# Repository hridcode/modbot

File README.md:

# ModBot

ModBot is a versatile RP2040 development board/robot base for mini robots. It is relatively small (~80x50mm), but packs a punch.

# Features

- RP2040 chip
- 2 L293D IC motor drivers (capable of driving 4 motors)
- MPU-6050 gyroscope + accelerometer IC
- 12 digital GPIO expansion pins 
- 4 ADC GPIO expansion pins
- 16 connections each for GND, +3.3V, and +5V (VBUS)
- Battery connection
- USB-C support (bare minimum for 2026)

# Pictures

|Schematic|PCB|
|---|---|
|||

# Notes

- If you are to use a battery with the board, you must include your own charging board and switch.
- I don't do FRC/FTC so I don't know if this would be something you can use for that.

---

Have fun!

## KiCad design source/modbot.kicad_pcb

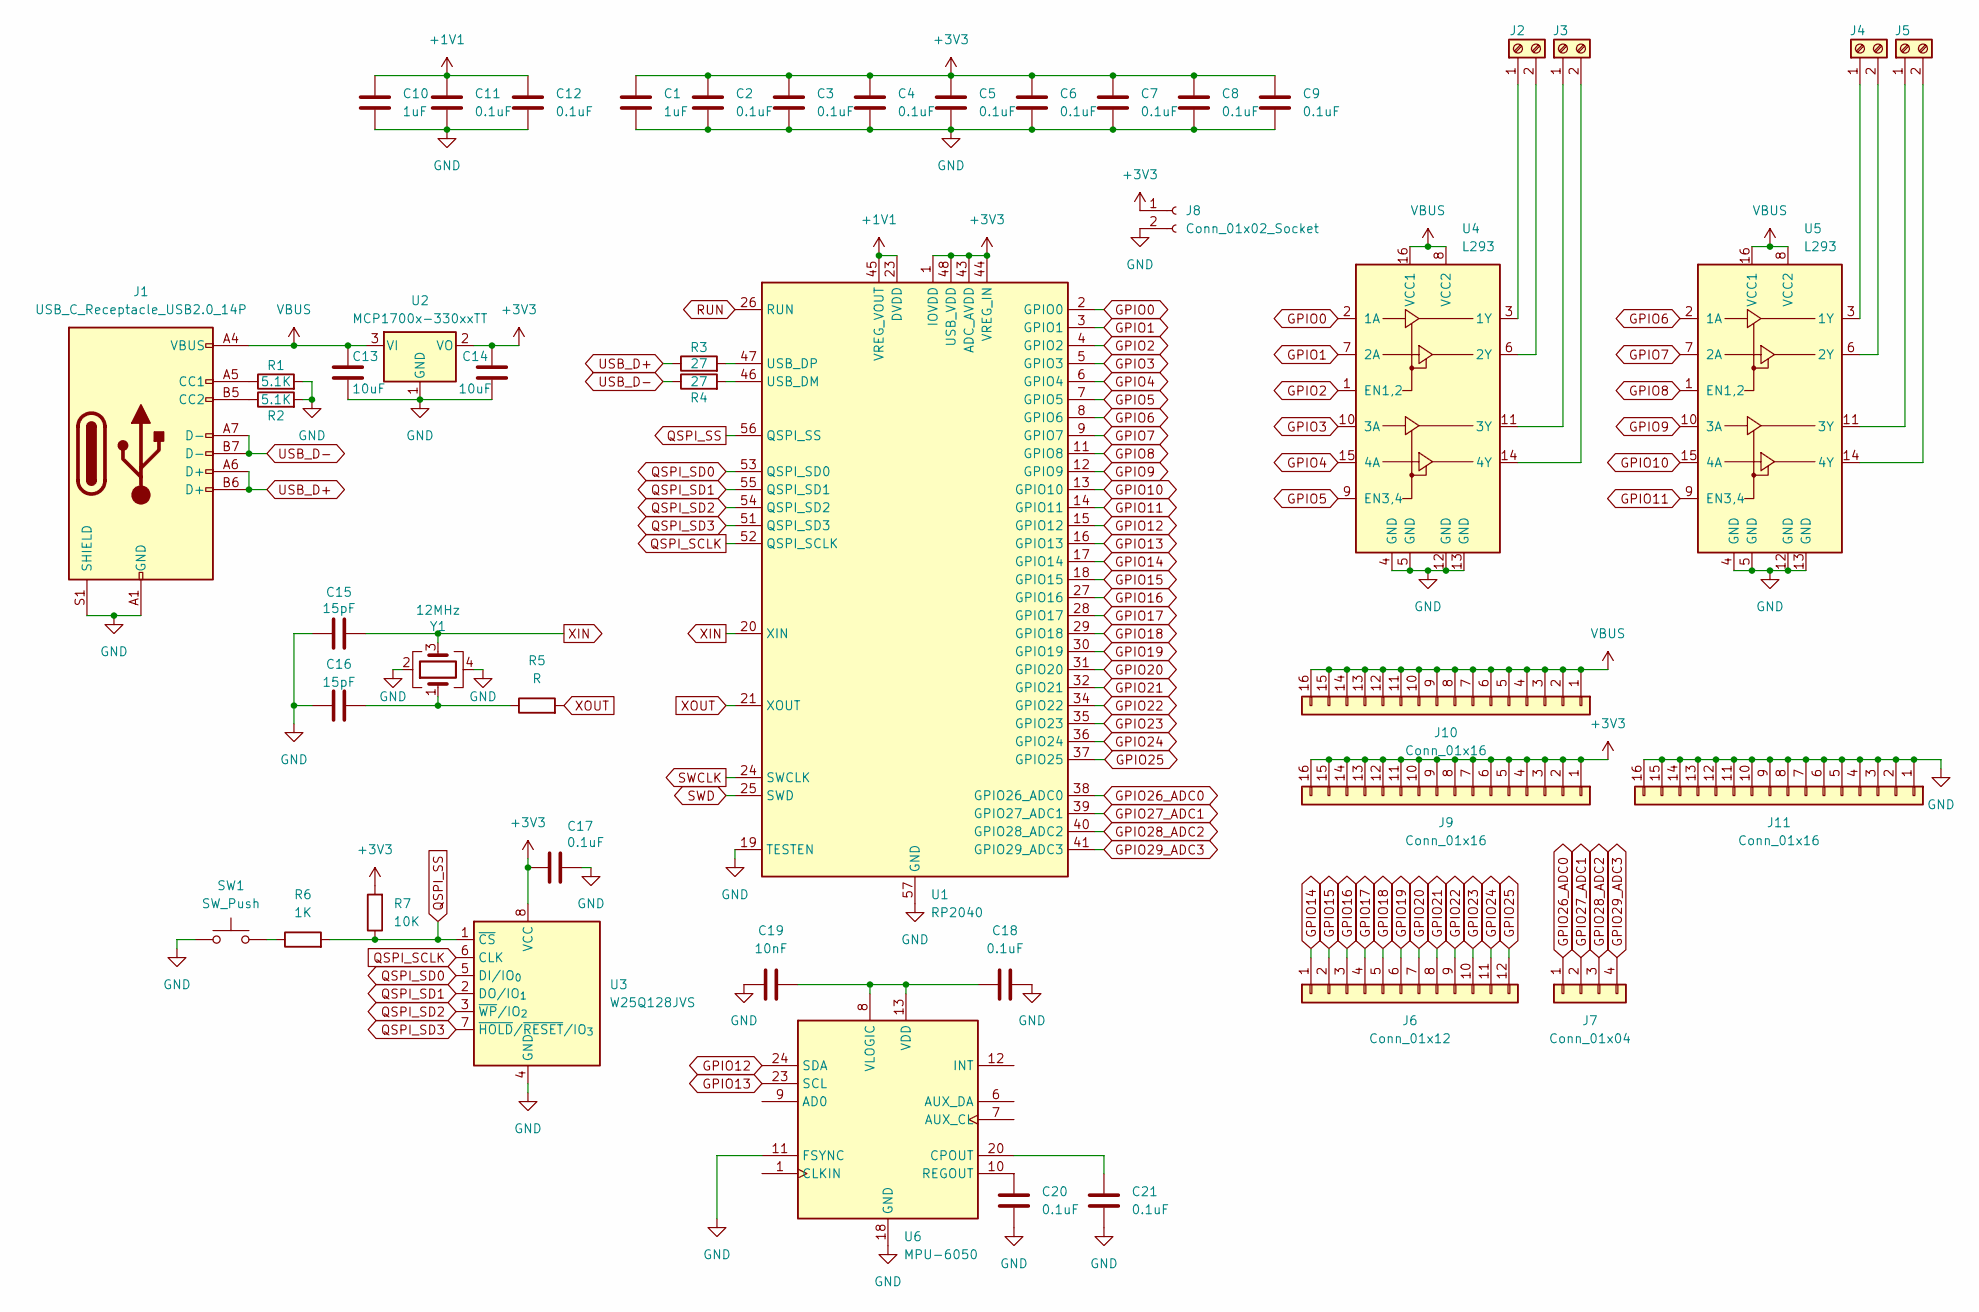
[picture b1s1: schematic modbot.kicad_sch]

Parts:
C1, C10: 1uF; C_0402_1005Metric
C2, C3, C4, C5, C6, C7, C8, C9, C11, C12, C17, C18, C20, C21: 0.1uF; C_0402_1005Metric
C13, C14: 10uF; C_0402_1005Metric
C15, C16: 15pF; C_0402_1005Metric
C19: 10nF; C_0402_1005Metric
J1: USB_C_Receptacle_USB2.0_14P; USB_C_Receptacle_HRO_TYPE-C-31-M-12
J2, J3, J4, J5: Screw_Terminal_01x02; TerminalBlock_MaiXu_MX126-5.0-02P_1x02_P5.00mm
J6: Conn_01x12; PinSocket_1x12_P2.54mm_Vertical
J7: Conn_01x04; PinSocket_1x04_P2.54mm_Vertical
J8: Conn_01x02_Socket; PinSocket_1x02_P2.54mm_Vertical
J9, J10, J11: Conn_01x16; PinSocket_1x16_P2.54mm_Vertical
R1, R2: 5.1K; R_0402_1005Metric
R3, R4: 27; R_0402_1005Metric
R5: R; R_0402_1005Metric
R6: 1K; R_0402_1005Metric
R7: 10K; R_0402_1005Metric
SW1: SW_Push; SW_SPST_PTS647_Sx38
U1: RP2040; QFN-56-1EP_7x7mm_P0.4mm_EP3.2x3.2mm
U2: MCP1700x-330xxTT; SOT-23
U3: W25Q128JVS; SOIC-8_5.3x5.3mm_P1.27mm
U4, U5: L293; DIP-16_W7.62mm
U6: MPU-6050; InvenSense_QFN-24_4x4mm_P0.5mm
Y1: 12MHz; Crystal_SMD_3225-4Pin_3.2x2.5mm

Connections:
+1V1: C10.1, C11.1, C12.1, U1.23 (DVDD), U1.45 (VREG_VOUT), U1.50 (DVDD)
+3V3: C1.1, C2.1, C3.1, C4.1, C5.1, C6.1, C7.1, C8.1, C9.1, C14.1, C17.1, J8.1, J9.1, J9.2, J9.3, J9.4, J9.5, J9.6, J9.7, J9.8, J9.9, J9.10, J9.11, J9.12, J9.13, J9.14, J9.15, J9.16, R7.2, U1.1 (IOVDD), U1.10 (IOVDD), U1.22 (IOVDD), U1.33 (IOVDD), U1.42 (IOVDD), U1.43 (ADC_AVDD), U1.44 (VREG_IN), U1.48 (USB_VDD), U1.49 (IOVDD), U2.2 (VO), U3.8 (VCC)
GND: C1.2, C2.2, C3.2, C4.2, C5.2, C6.2, C7.2, C8.2, C9.2, C10.2, C11.2, C12.2, C13.2, C14.2, C15.1, C16.1, C17.2, C18.2, C19.1, C20.1, C21.1, J1.A1 (GND), J1.A12 (GND), J1.B1 (GND), J1.B12 (GND), J1.S1 (SHIELD), J8.2, J11.1, J11.2, J11.3, J11.4, J11.5, J11.6, J11.7, J11.8, J11.9, J11.10, J11.11, J11.12, J11.13, J11.14, J11.15, J11.16, R1.2, R2.2, SW1.1, U1.19 (TESTEN), U1.57 (GND), U2.1 (GND), U3.4 (GND), U4.4 (GND), U4.5 (GND), U4.12 (GND), U4.13 (GND), U5.4 (GND), U5.5 (GND), U5.12 (GND), U5.13 (GND), U6.11 (FSYNC), U6.18 (GND), Y1.2, Y1.4
GPIO0: U1.2 (GPIO0), U4.2 (1A)
GPIO1: U1.3 (GPIO1), U4.7 (2A)
GPIO2: U1.4 (GPIO2), U4.1 (EN1,2)
GPIO3: U1.5 (GPIO3), U4.10 (3A)
GPIO4: U1.6 (GPIO4), U4.15 (4A)
GPIO5: U1.7 (GPIO5), U4.9 (EN3,4)
GPIO6: U1.8 (GPIO6), U5.2 (1A)
GPIO7: U1.9 (GPIO7), U5.7 (2A)
GPIO8: U1.11 (GPIO8), U5.1 (EN1,2)
GPIO9: U1.12 (GPIO9), U5.10 (3A)
GPIO10: U1.13 (GPIO10), U5.15 (4A)
GPIO11: U1.14 (GPIO11), U5.9 (EN3,4)
GPIO12: U1.15 (GPIO12), U6.24 (SDA)
GPIO13: U1.16 (GPIO13), U6.23 (SCL)
GPIO14: J6.1, U1.17 (GPIO14)
GPIO15: J6.2, U1.18 (GPIO15)
GPIO16: J6.3, U1.27 (GPIO16)
GPIO17: J6.4, U1.28 (GPIO17)
GPIO18: J6.5, U1.29 (GPIO18)
GPIO19: J6.6, U1.30 (GPIO19)
GPIO20: J6.7, U1.31 (GPIO20)
GPIO21: J6.8, U1.32 (GPIO21)
GPIO22: J6.9, U1.34 (GPIO22)
GPIO23: J6.10, U1.35 (GPIO23)
GPIO24: J6.11, U1.36 (GPIO24)
GPIO25: J6.12, U1.37 (GPIO25)
GPIO26_ADC0: J7.1, U1.38 (GPIO26_ADC0)
GPIO27_ADC1: J7.2, U1.39 (GPIO27_ADC1)
GPIO28_ADC2: J7.3, U1.40 (GPIO28_ADC2)
GPIO29_ADC3: J7.4, U1.41 (GPIO29_ADC3)
unnamed: C16.2, R5.1, Y1.1
unnamed: J1.A5 (CC1), R1.1
unnamed: J1.B5 (CC2), R2.1
unnamed: J2.1, U4.3 (1Y)
unnamed: J2.2, U4.6 (2Y)
unnamed: J3.1, U4.11 (3Y)
unnamed: J3.2, U4.14 (4Y)
unnamed: J4.1, U5.3 (1Y)
unnamed: J4.2, U5.6 (2Y)
unnamed: J5.1, U5.11 (3Y)
unnamed: J5.2, U5.14 (4Y)
unnamed: R6.1, SW1.2
unnamed: R4.2, U1.46 (USB_DM)
unnamed: R3.2, U1.47 (USB_DP)
unnamed: C21.2, U6.20 (CPOUT)
unnamed: C20.2, U6.10 (REGOUT)
unnamed: C18.1, C19.2, U6.8 (VLOGIC), U6.13 (VDD)
QSPI_SCLK: U1.52 (QSPI_SCLK), U3.6 (CLK)
QSPI_SD0: U1.53 (QSPI_SD0), U3.5 (DI/IO_{0})
QSPI_SD1: U1.55 (QSPI_SD1), U3.2 (DO/IO_{1})
QSPI_SD2: U1.54 (QSPI_SD2), U3.3 (~WP/IO_{2})
QSPI_SD3: U1.51 (QSPI_SD3), U3.7 (~HOLD/~RESET/IO_{3})
QSPI_SS: R6.2, R7.1, U1.56 (QSPI_SS), U3.1 (~CS)
RUN: U1.26 (RUN)
SWCLK: U1.24 (SWCLK)
SWD: U1.25 (SWD)
USB_D+: J1.A6 (D+), J1.B6 (D+), R3.1
USB_D-: J1.A7 (D-), J1.B7 (D-), R4.1
VBUS: C13.1, J1.A4 (VBUS), J1.A9 (VBUS), J1.B4 (VBUS), J1.B9 (VBUS), J10.1, J10.2, J10.3, J10.4, J10.5, J10.6, J10.7, J10.8, J10.9, J10.10, J10.11, J10.12, J10.13, J10.14, J10.15, J10.16, U2.3 (VI), U4.8 (VCC2), U4.16 (VCC1), U5.8 (VCC2), U5.16 (VCC1)
XIN: C15.2, U1.20 (XIN), Y1.3
XOUT: R5.2, U1.21 (XOUT)

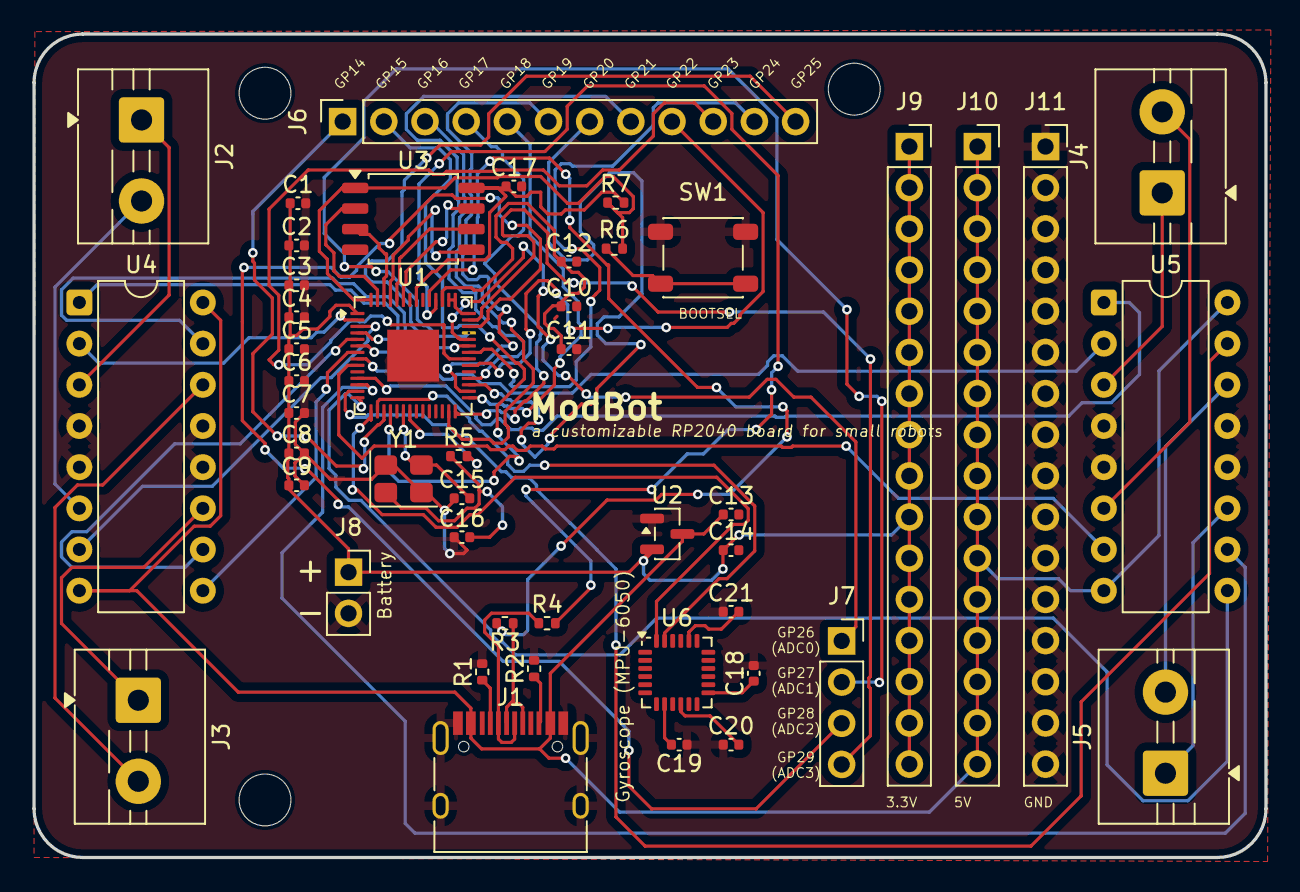
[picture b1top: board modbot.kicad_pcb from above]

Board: 2 copper layers, 76.0 x 50.8 mm, 47 parts (0 on the bottom side), 61 nets.

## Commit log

2026-03-22 Added source, production, BOM and README
2026-03-22 Updated README.md and BOM.csv
2026-03-22 Added photos and updated README.md
2026-03-22 Updated BOM.csv
2026-03-28 Replaced PCB gerber & source files with new versions
